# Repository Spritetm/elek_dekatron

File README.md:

What is this?
-------------

This repo contains the files for a Dekatron bandwidth spinner. It uses an ESP32-C3 to read
out a switch or other network device that talks over SNMP and spins a Dekatron according
to the data flowing over one of its network ports.

Directories in this repo
------------------------

 * case - Contains Fusion360 as well as step and stl files of the case.
 * pcb - Kicad project for the PCB of the spinner
 * firmware - Firmware for the ESP32-C3 in the device. Firmware was compiled using
   ESP-IDF v5.0.4 but you can probably use any v5.x version.

User manual
-----------

After building the PCB, the device needs to be flashed. This can be done by plugging
the USB-C port into a PC while holding the button on the back of the device, then 
flashing as normal. Unplug and replug to start the firmware. After the first succesful
flash, you generally don't need to hold the button when re-flashing.

This device needs to be connected to an USB-PD power supply that can supply 9V or 
more to activate the HV power supply for the Dekatron. If not attached to a 
compatible power supply (e.g. when plugged into a computer), D9 will blink and the 
Dekatron will stay off. The rest of the device will still work, that is, you can
still configure WiFi and SNMP credentials as usual.

On first startup, WiFi needs to be configured. To do this, the device will show
a WiFi access point called 'dekatron'. You can connect to this using a phone or laptop
and it will automatically direct you to a captive webpage where you can select an
access point and enter its password. If the redirect doesn't happen, simply open
a browser and go to http://192.168.4.1/wifi . After you've entered this, the Dekatron
will try to show its best impression of the IP address it got; if you have issues
decyphering this, you can try either connecting to the serial port to see the IP it 
got or checking the DHCP lease table on your router.

The Dekatron will remember the WiFi network and password on subsequent power-ups.
If for some reason you need to change WiFi credentials (e.g. because the original
network is not available anymore, after boot-up simply press and hold the button on
the back of the device for more than 3 seconds, and the 'dekatron' WiFi access point
will show up again.

If you use a webbrowser to connect to the IP, you can configure the SNMP credentials.
Note that you will probably need to change the IP address if your switch, but often the
default community and OIDs will work to use the information of the first network port.
The last decimal of the OID indicates the network port, so increade that to get
another one. Note that some switches don't start counting ports from 1; e.g. my Cisco
starts at 49 instead so the OID for incoming octets on the 2nd network port
I use is .1.3.6.1.2.1.2.2.1.10.50

Here, you can also configure the bandwidth that makes the dekatron spin fastest. You 
can set this to lower than your actual Internet connection can handle; it will simply
spin at its fastests speed for any bandwidth above. Note the bandwidth is in bits 
per second; if you know the bandwidth in bytes per second, simply multiply that by eight.

Finally, you can set a rotation. Some effects (for now only the bit where it shows the
devices IP on the dekatron) assume a a rotation of the physical dekatron. If this is 
wrong, you can adjust it here. Note that the position detection circuit is a bit finnicky,
so depending on your dekatron you may not be able to get this to work stably.

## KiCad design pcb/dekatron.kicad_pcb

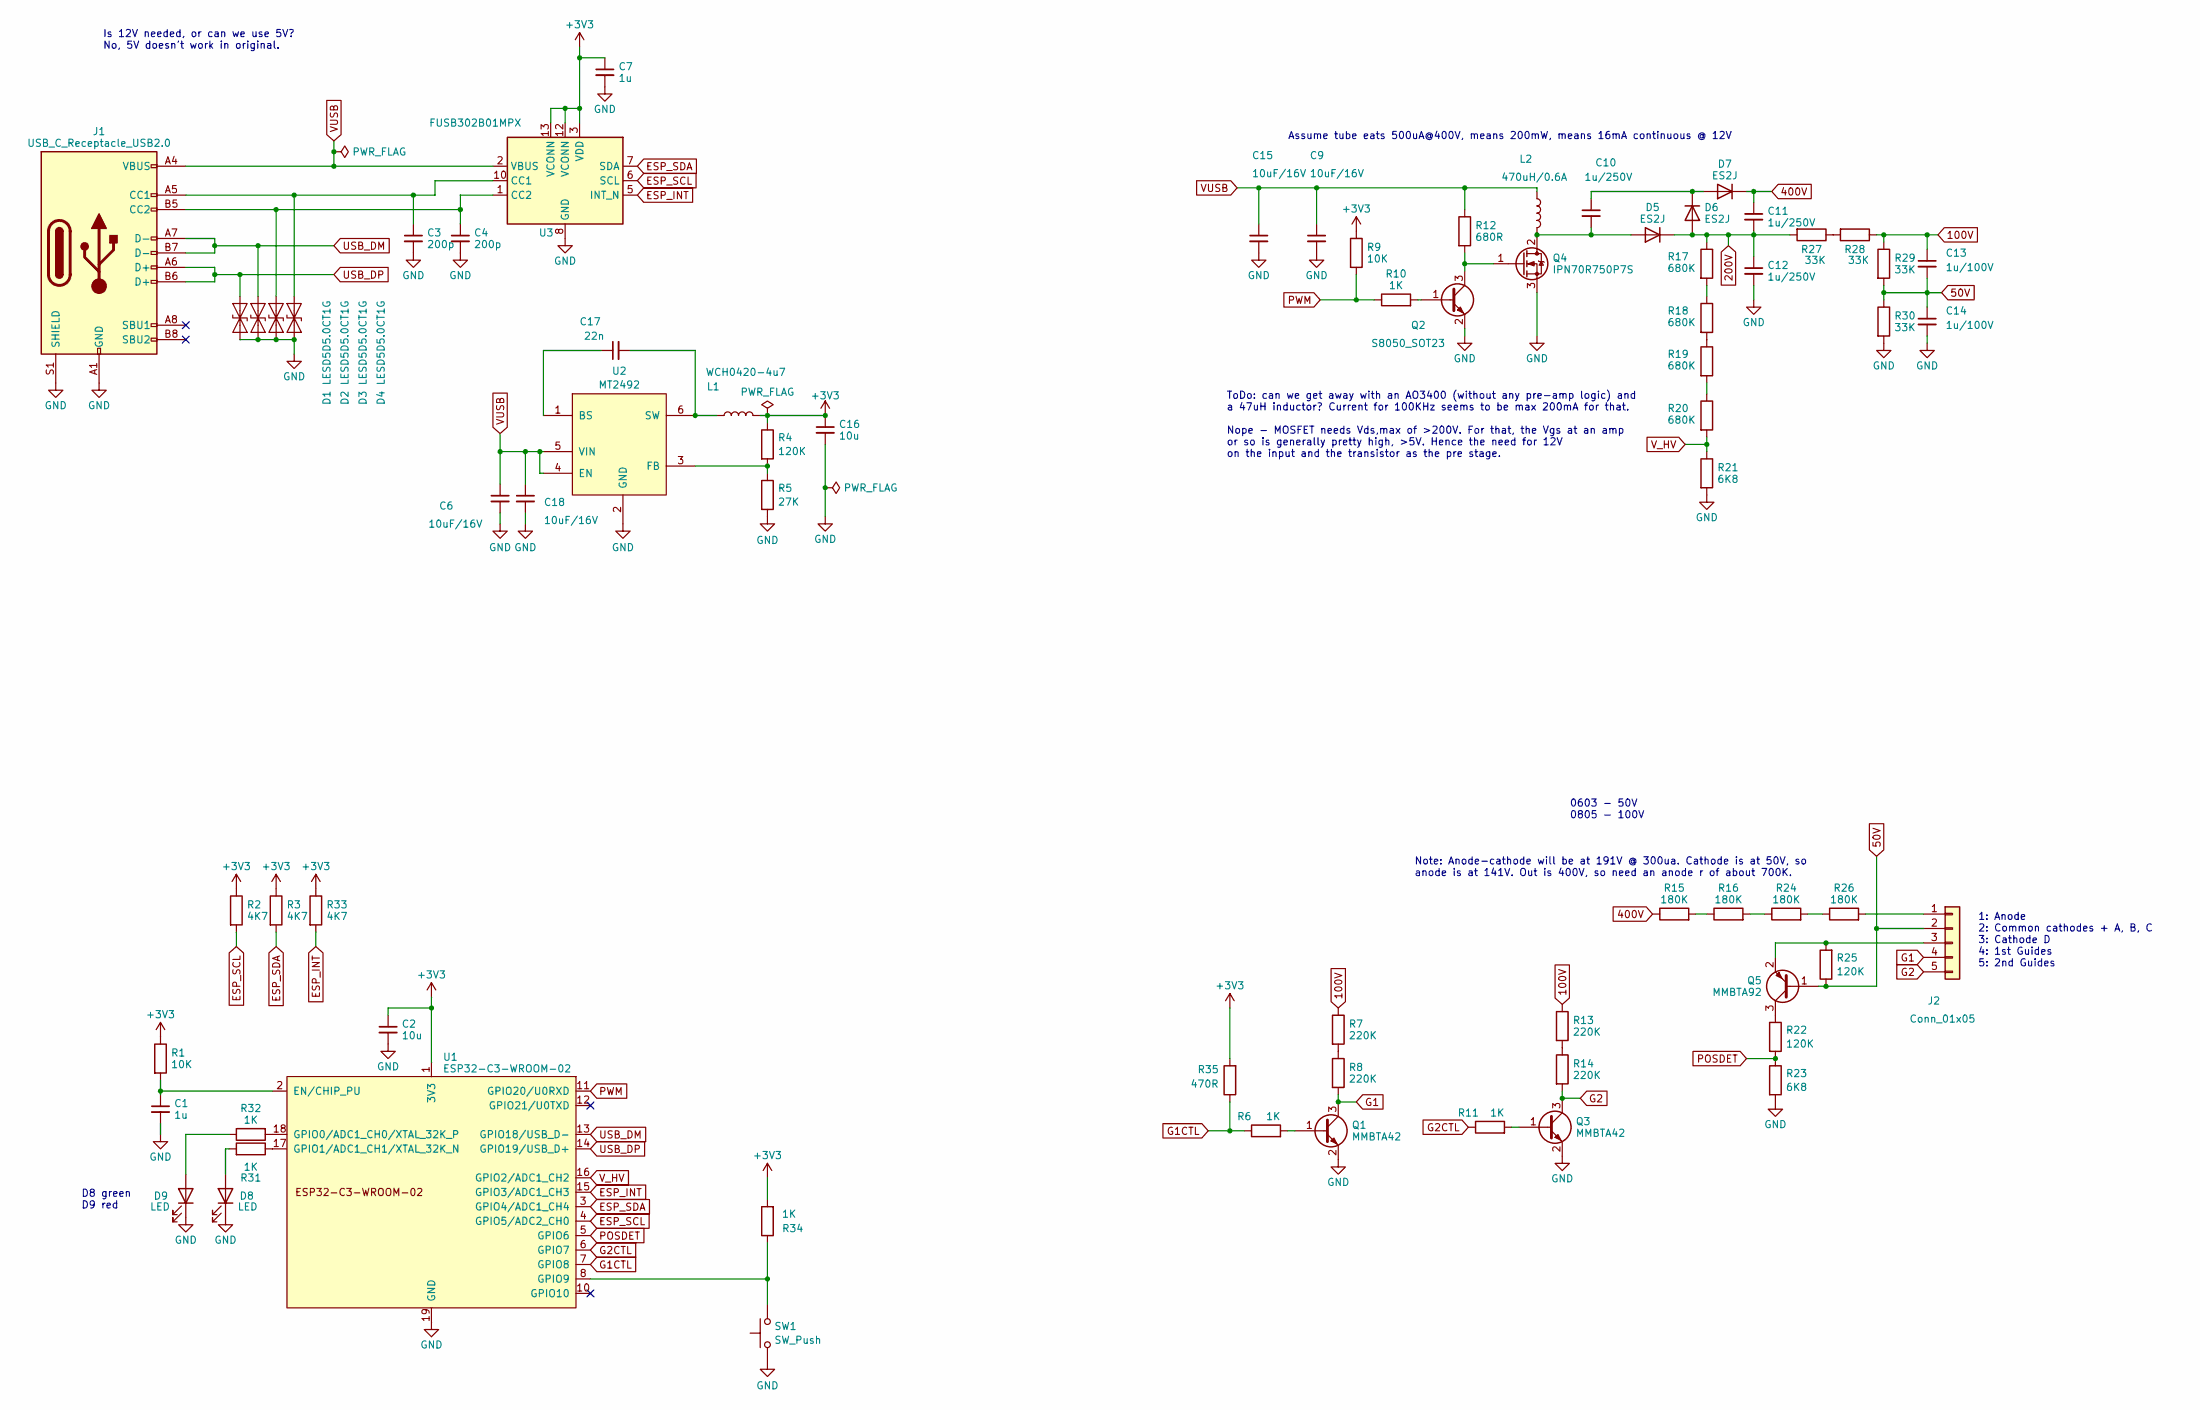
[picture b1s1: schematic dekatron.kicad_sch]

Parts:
C1, C7: 1u; C_0603_1608Metric
C2, C16: 10u; C_0805_2012Metric
C3, C4: 200p; C_0603_1608Metric
C6, C9, C15, C18: 10uF/16V; C_0805_2012Metric
C10, C11, C12: 1u/250V; C_2220_5650Metric
C13, C14: 1u/100V; C_1210_3225Metric
C17: 22n; C_0603_1608Metric
D1, D2, D3, D4: LESD5D5.0CT1G; D_SOD-523
D5, D6, D7: ES2J; D_SMA
D8, D9: LED; LED_0603_1608Metric
J1: USB_C_Receptacle_USB2.0; USB_C_Receptacle_HRO_TYPE-C-31-M-12
J2: Conn_01x05; PinHeader_1x05_P2.54mm_Vertical
L1: WCH0420-4u7; L_Chilisin_BMRA00040420
L2: 470uH/0.6A; Inductor_CYH127
Q1, Q3: MMBTA42; SOT-23
Q2: S8050_SOT23; SOT-23
Q4: IPN70R750P7S; PG-SOT-223
Q5: MMBTA92; SOT-23
R1, R9: 10K; R_0603_1608Metric
R2, R3, R33: 4K7; R_0603_1608Metric
R4, R22, R25: 120K; R_0603_1608Metric
R5: 27K; R_0603_1608Metric
R6, R10, R11, R31, R32, R34: 1K; R_0603_1608Metric
R7, R8, R13, R14: 220K; R_0603_1608Metric
R12: 680R; R_0603_1608Metric
R15, R16, R24, R26: 180K; R_0603_1608Metric
R17, R18, R19, R20: 680K; R_0603_1608Metric
R21, R23: 6K8; R_0603_1608Metric
R27, R28, R29, R30: 33K; R_0603_1608Metric
R35: 470R; R_0603_1608Metric
SW1: SW_Push; SW_SPST_Omron_B3F-315x_Angled
U1: ESP32-C3-WROOM-02
U2: MT2492; SOT-23-6
U3: FUSB302B01MPX; WQFN-14-1EP_2.5x2.5mm_P0.5mm_EP1.45x1.45mm

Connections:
50V: C13.2, C14.1, J2.2, Q5.1 (B), R25.1, R29.2, R30.1
100V: C13.1, R7.1, R13.1, R28.1, R29.1
200V: C11.2, C12.1, D5.1 (K), D6.2 (A), R17.1, R27.2
400V: C11.1, D7.1 (K), R15.1
+3V3: C2.1, C7.1, C16.1, L1.2, R1.1, R2.1, R3.1, R4.1, R9.1, R33.1, R34.2, R35.2, U1.1 (3V3), U3.3 (VDD), U3.4 (VDD), U3.12 (VCONN), U3.13 (VCONN)
ESP_INT: R33.2, U1.15 (GPIO3/ADC1_CH3), U3.5 (INT_N)
ESP_SCL: R2.2, U1.4 (GPIO5/ADC2_CH0), U3.6 (SCL)
ESP_SDA: R3.2, U1.3 (GPIO4/ADC1_CH4), U3.7 (SDA)
G1: J2.4, Q1.3 (C), R8.2
G1CTL: R6.1, R35.1, U1.7 (GPIO8)
G2: J2.5, Q3.3 (C), R14.2
G2CTL: R11.1, U1.6 (GPIO7)
GND: C1.2, C2.2, C3.2, C4.2, C6.2, C7.2, C9.2, C12.2, C14.2, C15.2, C16.2, C18.2, D1.1 (A1), D2.1 (A1), D3.1 (A1), D4.1 (A1), D8.1 (K), D9.1 (K), J1.A1 (GND), J1.A12 (GND), J1.B1 (GND), J1.B12 (GND), J1.S1 (SHIELD), Q1.2 (E), Q2.2 (E), Q3.2 (E), Q4.3 (S), R5.2, R21.2, R23.2, R30.2, SW1.1, U1.9 (GND), U1.19 (GND), U2.2 (GND), U3.8 (GND), U3.9 (GND), U3.15 (GND)
unnamed: C4.1, D3.2 (A2), J1.B5 (CC2), U3.1 (CC2), U3.14 (CC2)
unnamed: C3.1, D4.2 (A2), J1.A5 (CC1), U3.10 (CC1), U3.11 (CC1)
unnamed: C10.2, D5.2 (A), L2.2, Q4.2 (D)
unnamed: C10.1, D6.1 (K), D7.2 (A)
unnamed: D8.2 (A), R31.2
unnamed: D9.2 (A), R32.1
unnamed: J2.1, R26.2
unnamed: J2.3, Q5.2 (E), R25.2
unnamed: Q1.1 (B), R6.2
unnamed: Q2.1 (B), R10.2
unnamed: Q2.3 (C), Q4.1 (G), R12.2
unnamed: Q3.1 (B), R11.2
unnamed: Q5.3 (C), R22.1
unnamed: R7.2, R8.1
unnamed: R13.2, R14.1
unnamed: R15.2, R16.1
unnamed: R16.2, R24.1
unnamed: R17.2, R18.1
unnamed: R18.2, R19.1
unnamed: R19.2, R20.1
unnamed: R24.2, R26.1
unnamed: R27.1, R28.2
unnamed: C1.1, R1.2, U1.2 (EN/CHIP_PU)
unnamed: R32.2, U1.18 (GPIO0/ADC1_CH0/XTAL_32K_P)
unnamed: R31.1, U1.17 (GPIO1/ADC1_CH1/XTAL_32K_N)
unnamed: R34.1, SW1.2, U1.8 (GPIO9)
unnamed: C17.1, U2.1 (BS)
unnamed: R4.2, R5.1, U2.3 (FB)
unnamed: C17.2, L1.1, U2.6 (SW)
POSDET: R22.2, R23.1, U1.5 (GPIO6)
PWM: R9.2, R10.1, U1.11 (GPIO20/U0RXD)
USB_DM: D2.2 (A2), J1.A7 (D-), J1.B7 (D-), U1.13 (GPIO18/USB_D-)
USB_DP: D1.2 (A2), J1.A6 (D+), J1.B6 (D+), U1.14 (GPIO19/USB_D+)
VUSB: C6.1, C9.1, C15.1, C18.1, J1.A4 (VBUS), J1.A9 (VBUS), J1.B4 (VBUS), J1.B9 (VBUS), L2.1, R12.1, U2.4 (EN), U2.5 (VIN), U3.2 (VBUS)
V_HV: R20.2, R21.1, U1.16 (GPIO2/ADC1_CH2)

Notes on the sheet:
D8 green D9 red
Is 12V needed, or can we use 5V? No, 5V doesn't work in original.
Assume tube eats 500uA@400V, means 200mW, means 16mA continuous @ 12V
ToDo: can we get away with an AO3400 (without any pre-amp logic) and a 47uH inductor? Current for 100KHz seems to be max 200mA for that. Nope - MOSFET needs Vds,max of >200V. For that, the Vgs at an amp or so is generally pretty high, >5V. Hence the need for 12V on the input and the transistor as t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
1: Anode 2: Common cathodes + A, B, C 3: Cathode D 4: 1st Guides 5: 2nd Guides
Note: Anode-cathode will be at 191V @ 300ua. Cathode is at 50V, so anode is at 141V. Out is 400V, so need an anode r of about 700K.
0603 - 50V 0805 - 100V

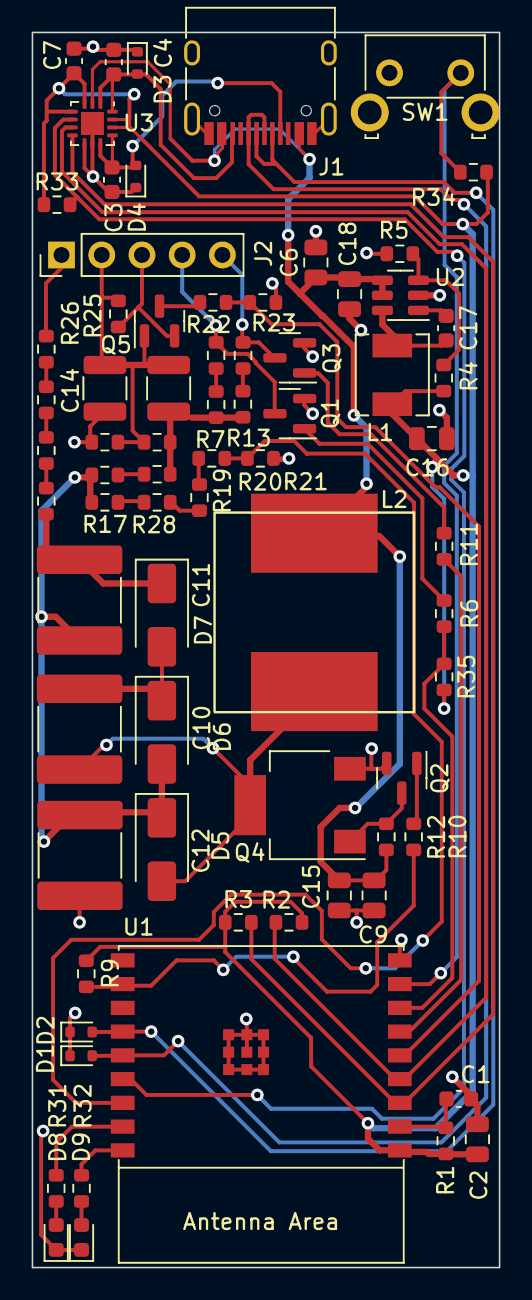
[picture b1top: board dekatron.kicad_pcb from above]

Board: 2 copper layers, 29.5 x 78.0 mm, 73 parts (0 on the bottom side), 48 nets.

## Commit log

2023-07-25 Initial commmit.
2023-11-20 Small fix to make the boot button succesfully boot into download mode
2023-11-20 Lots of fixes, add button support, add LED support, hook up SNMP to Dekatron
2023-11-20 Add files for 3d-printed case
2023-11-20 Add schematic pdf
2023-11-20 Write readme
2023-11-20 Add licenses

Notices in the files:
pcb/dekatron.kicad_pcb:
(C) 2023 SPRITESMODS.COM
